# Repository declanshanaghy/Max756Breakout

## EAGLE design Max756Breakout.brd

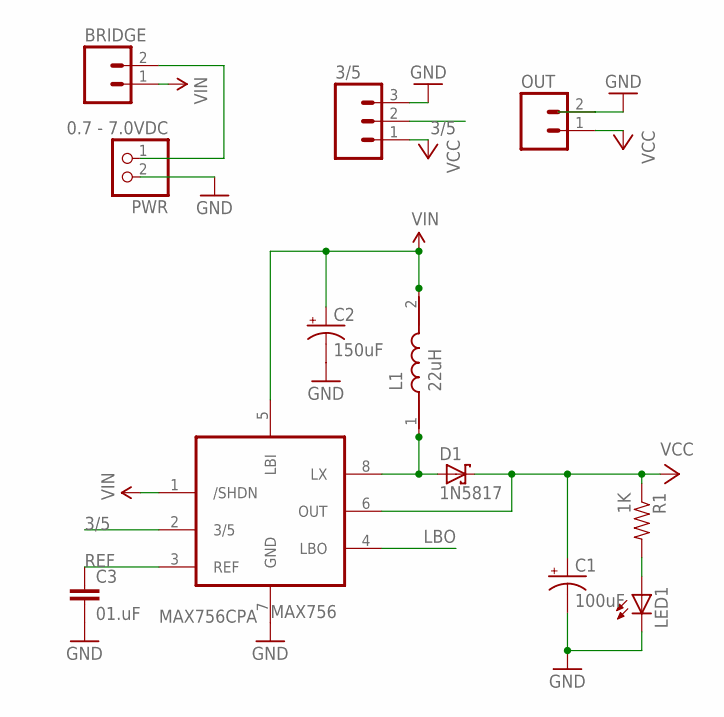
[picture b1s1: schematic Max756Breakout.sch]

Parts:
3/5: M03LOCK; 1X03_LOCK
BRIDGE: M02LOCK; 1X02_LOCK
C1: 100uF; CPOL-RADIAL-10UF-25V
C2: 150uF; CPOL-RADIAL-10UF-25V
C3: 01.uF; CAP-PTH-SMALL2
D1: 1N5817; F126Z12
L1: 22uH; 82114R
LED1: LED3MM
MAX756: MAX756CPA; DIL08
OUT: M02LOCK; 1X02_LOCK
PWR: 0.7 - 7.0VDC; JST-PH-2-THM-RA
R1: 1K; AXIAL-0.2

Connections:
3/5: 3/5.2, MAX756.2 (3/5)
GND: 3/5.3, C1.2 (-), C2.2 (-), C3.2, LED1.K (C), MAX756.7 (GND), OUT.2, PWR.2 (1)
L1: D1.A, L1.1, MAX756.8 (LX)
LBO: MAX756.4 (LBO)
unnamed: BRIDGE.2, PWR.1 (2)
unnamed: LED1.A, R1.P$2 (2)
REF: C3.1, MAX756.3 (REF)
VCC: 3/5.1, C1.1 (+), D1.C, MAX756.6 (OUT), OUT.1, R1.P$1 (1)
VIN: BRIDGE.1, C2.1 (+), L1.2, MAX756.1 (/SHDN), MAX756.5 (LBI)

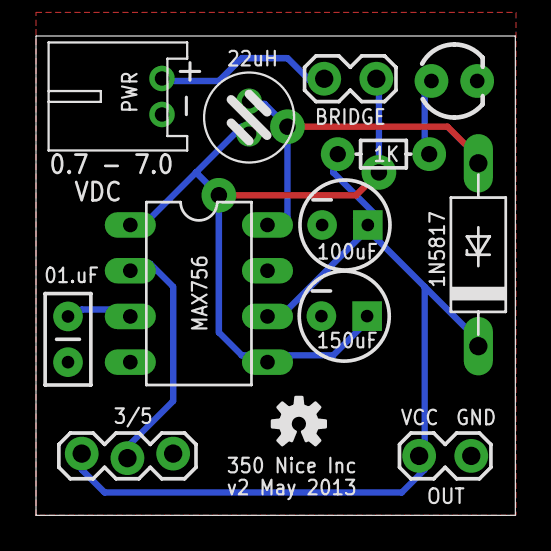
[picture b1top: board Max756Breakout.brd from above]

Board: 2 copper layers, 26.6 x 26.6 mm, 13 parts (0 on the bottom side), 8 nets.

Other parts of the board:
U$1: OSHW-LOGO-S

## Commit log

2013-05-22 Replaced some parts with better real world representations
2013-05-22 Changed voltage selector to a jumper
2013-05-23 Only breakout 2 pins for ease of use
2013-05-24 v1 completed. Needs some minor tweaks
2013-05-24 Adding v1 gerber files
2013-05-24 Added LED for v2
2013-06-03 Exported PDF schematic

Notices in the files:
parts and their libraries:
SparkFun-Capacitors: Licensing: CC v3.0 Share-Alike You are welcome to use this library for commercial purposes.
